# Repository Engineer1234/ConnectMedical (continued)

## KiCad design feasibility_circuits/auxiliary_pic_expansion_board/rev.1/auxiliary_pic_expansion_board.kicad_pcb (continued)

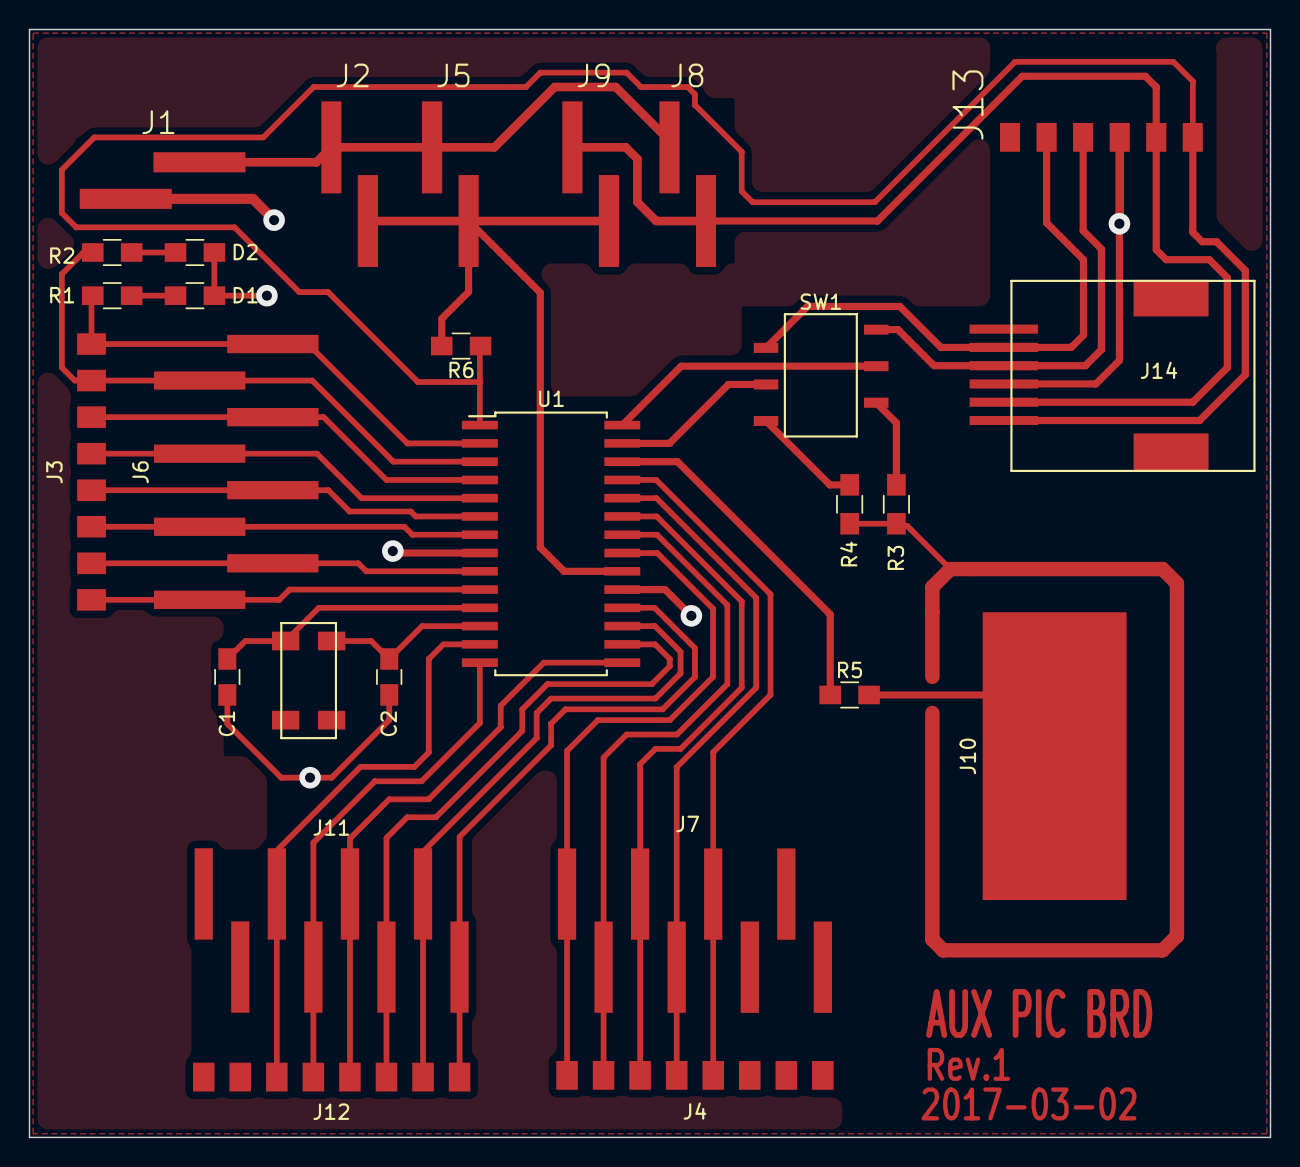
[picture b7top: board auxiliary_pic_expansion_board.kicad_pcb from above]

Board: 2 copper layers, 86.2 x 77.0 mm, 27 parts (0 on the bottom side), 37 nets.

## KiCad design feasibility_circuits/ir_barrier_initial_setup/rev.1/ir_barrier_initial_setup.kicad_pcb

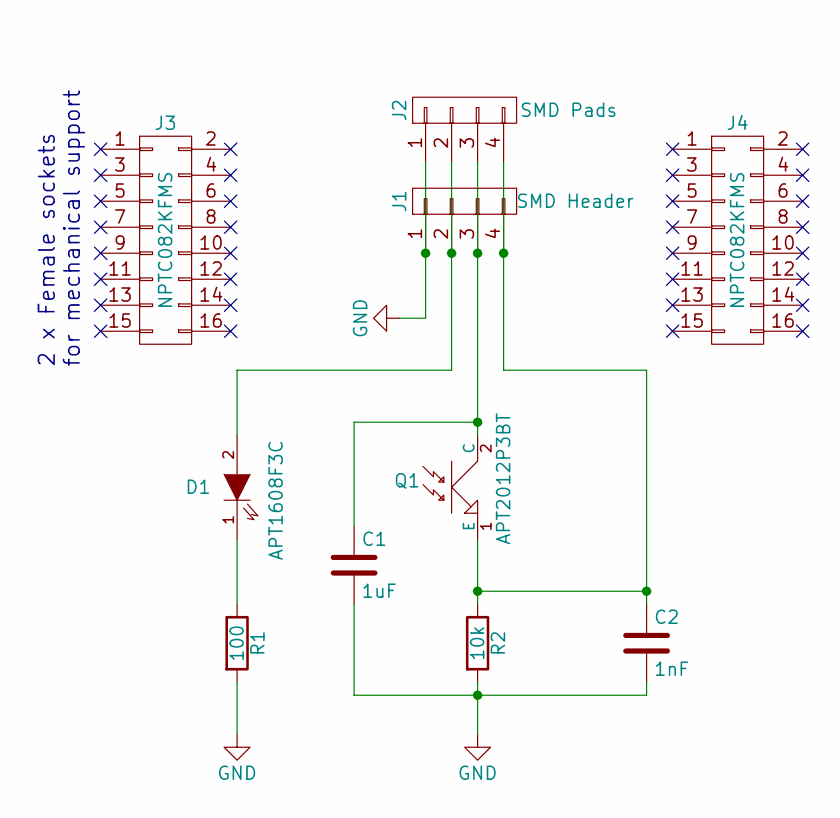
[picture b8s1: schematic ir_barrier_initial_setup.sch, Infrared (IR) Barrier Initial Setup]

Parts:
C1: 1uF; C_0805_HandSoldering
C2: 1nF; C_0805_HandSoldering
D1: APT1608F3C; LED_APT1608F3C
J1: SMD Header; Sullins_SMD_pin_header_1x4_GBC36SABN-M30
J2: SMD Pads; wire_solder_pad_2.54mm_1x4
J3, J4: NPTC082KFMS; Sullins_SMD_2x08_NPTC082KFMS-RC
Q1: APT2012P3BT; Phototransistor_APT2012P3BT
R1: 100; R_0805_HandSoldering
R2: 10k; R_0805_HandSoldering

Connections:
GND: C1.2, C2.2, J1.1, J2.1, R1.2, R2.2
unnamed: C1.1, J1.3, J2.3, Q1.2 (C)
unnamed: C2.1, J1.4, J2.4, Q1.1 (E), R2.1
unnamed: D1.1 (K), R1.1
unnamed: D1.2 (A), J1.2, J2.2

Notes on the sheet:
2 x Female sockets for mechanical support

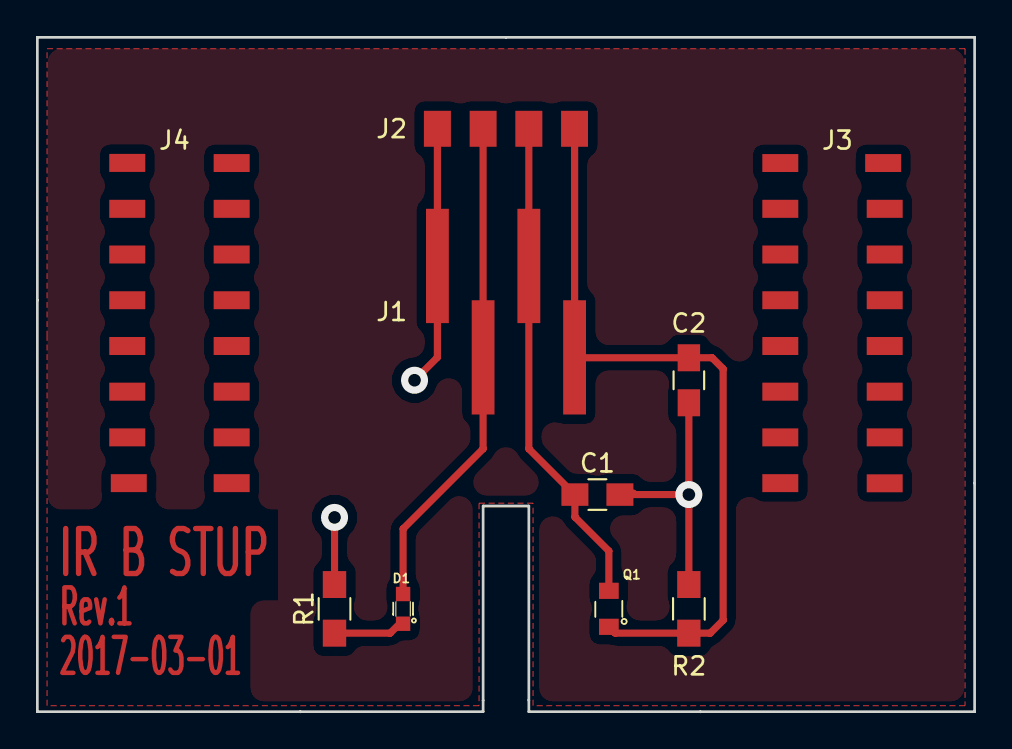
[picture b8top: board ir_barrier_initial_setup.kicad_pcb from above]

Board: 2 copper layers, 52.1 x 37.5 mm, 10 parts (0 on the bottom side), 5 nets.

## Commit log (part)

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2017-02-22 Added schematic for processor board, along with libraries and basic folder structure.
2017-02-22 Addded guard trace for cap-sense pad
2017-02-23 Added prototype board for original IR solution, and imported the Connect Trial footprints in the libraries folder. Also added updated gitignore files for the IR and PIC boards.
2017-02-27 Battery benchmarking
    First commit. Initial infrastructure.
2017-02-28 Battery benchmarking update
    Routed PCB, improvements to structure/naming
2017-02-28 Battery benchmarking update
    PCB ready for review
2017-03-02 Review and organisation
    Review of Auxiliary PIC and IR barrier setup board. Organisation of
    resources.
2017-04-09 2V regulator module
2017-04-18 Four constant current loads module
    Four constant current loads module
2017-04-28 Updated component libraries in battery board to use relative paths
2017-04-28 Finished layout of the TPS61220 regulator board
2017-04-28 Completed initial draft of layout of battery board
2017-04-28 Added holder for Lithium-Ion cell to battery board
2017-04-28 Added files forgotten in last commit.
2017-05-02 Completed schematic for s-1206 LDO prototype board.
2017-05-02 Completed initial draft of layout for S-1206 LDO prototype board
2017-05-03 Added zip files of gerber files sent to Cogra for production for the S-1206 and battery board
2017-05-03 Added gitignore file for feasibility circuits folder
2017-05-03 Removed kicad_pcb-bak files from git version tracking.
2017-05-05 Completed layout of constant current load PCB, the zip file sent for production is also included
2017-05-05 Completed schematic for TPS624731 step-down prototype board
2017-05-05 Created initial project draft for AP3915A 2V regulator prototype board.
2017-05-08 Completed schematic for the AP3915A based 2V regulator prototype board.
2017-05-13 Completed intial draft of TPS627431 2V regulator prototype board
2017-07-26 Created folder Structure. Blank Altium Project. Added Blank Layout File Added Component footprint and symbols. Added Sheet hierarchy with Sheets for: 1.CPU Board 2.Power Management 3.Connectors 4.I/O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
2017-07-26 Test : Updated Block Diagram
2017-07-26 Test commit from Altium
2017-07-26 Test, from Altium
2017-07-27 Create and Update components required on Boost regulator
2017-07-27 - Create extra SCH components for Buck regulator - Update PWR_MGMT Schematics accordingly
2017-07-27 - Create extra SCH components for USB protector and Charger controller - Update PWR_MGMT Schematics accordingly - Todo: Add footprints to PCB library (0402, 0603, etc)
2017-07-27 Altium SVN status Check
2017-07-27 - Update all passive components by adding PCB link ins SCHlib - Update PWR_MGMT with corresponding components
2017-07-27 - Add CPU and connector for OLED on CPU_BRD - Add IR Barrier on IO_BRD - Create components as necesarry and added to SCHLib
2017-07-31 - Add 2.2nF component for Touch sensor in SCHLIB - Add Touch sensor capacitor in CPU_BRD - Label CPU connections in CPU_BRD
2017-07-31 - Create components for battery connector and touch connector - Add Battery connector to PWR_MGMT - Add Touch connector to CPU_BRD
2017-07-31 - Reacommodate Battery connector on CONN - Create (draft) components Programming pads and testing points - Initiate usage of programming pads and testing points in CONN
2017-07-31 (Bug) Correct TP part as No-BOM and update CONN
2017-08-01 Update Touch sensor connector specs using the verified one sent by Oliver Chu
2017-08-02 - Add "DigikeyPartNumber" id in all used components from SCHlib then propagate to project - Create first version of PCB based on the Step file provided (will be updated)
2017-08-03 Update USB connector: Create component and update schematics as well
2017-08-03 - Correct spacing in SCH for IO board - Initialize component PCB placement on EFM1 - Add Cost of components of BOM in new sheet
2017-08-04 - Update component so Digi-Key Part Number use multiples of 1K to buy - Separate component 0603 10uF into 10uF-4V and 10uF-10V - Update Schematics - Update BOM and BOM cost
2017-08-04 - Remove silk layer labels of Cypress Module component - Change layer of all silk layer on PCB Layout
2017-08-08 Add STBC03 component: Li-Ion linear battery charger with LDO and load switches
2017-08-10 - Update PCB with non-hole version in USB section - Finish - Update labels of componenets - Preposition all components to check saturation in the board
2017-08-14 Correct Capacitance in IN and SYS section of Power Management
2017-08-14 Reduce dimensions of 0402 capacitor components so they are IPC High density compliant
2017-08-16 Creation of component for I2C Memory PCA9571GUX & LE2464C: creation of components and usage in Schematics
2017-08-16 Update Testing points and CPU programming points: 1mm pad, 0.6mm via with 0.3mm holes
2017-08-16 Increase current to 89% of Capacity: 34.3mA, by changing ISET resistor to 5.6Kohm
2017-08-16 - Reallocation of components to have a view after the change to I2C components - Update BOM with costs
2017-08-18 - Update PCB board according to latest specifications (2 strips on the side) - Update Light Barrier mechanism: use 0ohm resistors
2017-08-22 - Update circuit for IR barrier - Add testing TRX - Update components - Update position of components on Layout - Update BOM
2017-08-22 - Add R20 to reduce current consumption to MOUNT_SWITCH signal in MCU - Allocate component - Update BOM
2017-08-22 - Keep Buck converter always ON: Connect EN to VIN (Datasheet reference)
2017-08-23 - Apply changes from recommendations on Schematics review: Naming, connections, and specifications of values R1&R2
2017-08-23 - Bug: Use V_BATT on Mount Switch - Create LED components - Create and replace L1 with recommended 10uH
2017-08-24 - Add latest 3D views - Add comments regarding the Mounting Switch
2017-08-24 - Add FET mechanism proposal (parts not finalized)
2017-08-24 cosmetic changes in schematics. Changed Port name for Mounting Switch to Wake_up. Moved USB symbol to Top level. Added RES to Wake up FET Clean up.
2017-08-25 - Update Programming component (5 pins dimensions)
2017-08-25 - Add ESD protection on the switches
2017-08-31 - Correction of description on ESD diode
2017-09-07 Changed File version from “A” to “B” Updated I/O board to remove extra 0 Ohm RES Changed USB connector to USB3155 Added Step files for components
2017-09-07 Adding tag folder
2017-09-07 Changed VDD from 2V to 3V Changed step files and solder mask size on few components
2017-09-07 Added step Files
2017-09-07 Added Note for removed 2V regulator.
2017-09-07 Un-versioned BOM template files Fixing SVN issues
2017-09-13 Project template for EFM1 hybrid board
2017-09-13 Added Test points. Added foot prints for jumpers and GND test points.
2017-09-13 Placed MCU , Modified footprint for LED , need needs to be verified. Added step file for Battery connector.
    //Kartik
2017-09-14 Changed origin to centre of hole Added new component - Touch connector 1003-1009-1-ND placed Fidu placed MCU and Touch conn
2017-09-14 Moved mounting hole and hence the origin too. Added grid lines
2017-09-14 - Add VEMT2003X01 component - Remove STEP from VEMT2003X01, VEMT2000X01, and VSMB2000X01 (still need to find correct reference)
2017-09-14 Buck converter removed from Layout Components made Graphical
2017-09-14 Revision and creation of components: APT1608F3C,APT2012P3BT,TEMD7100X01,VSOP38336,TEMT7100X01,TSOP57256HTT1,VEMT2000X01
2017-09-14 Modified Footprint for BGA , Added via in Pad based on the reference designs from ST modified Footprint for other pars to remove DRC errors
2017-09-15 Updated footprints to remove rule conflicts Updated footprints to remove rule conflicts
2017-09-15 Commit end of the day: IR LED and Switches laid out. 9V regulator.
2017-09-18 Create components: 74AUP1G86FS3-7, Switch toggle, headers 14x2 and 9x2, touch pad and Orange LED
2017-09-18 Update component available provider: headers 14x2
2017-09-19 Swapped the pins on the Batt connector . Finished the layout for Batt charger
2017-09-19 Fixed Missing Step file of enclosure
2017-09-19 Changed Step file for LED.
2017-09-20 Switched wake-up gate voltage from 3V to VCC_VCC. based on Spice simulation Layout
2017-09-20 Values for R & C for Wake up delay set to 82K and 22uF. change in Footprint of the 22uF Cap to 0603
2017-09-20 Layout , Before removing I2C CAPs
2017-09-20 End of day commit
2017-09-21 Added footprint for M24256-DFCS6TP/K 256K memory
2017-09-21 Changed Position of OLED Con. Changed memory.
2017-09-22 Switched SNS_Touch and Ai_LASER_CURRENT pins ( 22 and 14)
2017-09-22 Before swapping LED Pins
2017-09-22 Changed solder mask size on few components due to DRC errors
2017-09-25 Added Draftman files
2017-09-25 Add Step file for VEMT2000, VSMB2000 and VEMT2003X01
2017-09-25 Production files generated. removed Old BOM files.
2017-09-26 Added Testpoint info to Draftman page
2017-09-26 corrected output file name for Assembly Drawings
2017-09-26 Updated PCB based on enclosure Step Files from Even
2017-09-26 latest PCB Rules and DXP Preferences
2017-09-26 re-saved project
2017-09-26 Updated Sch to include extra IR pairs added Jumper headers.
2017-09-26 Update for errors.
2017-09-26 corrected "Unique Identifiers Errors"
2017-09-27 Updated with board shape experiment
2017-09-27 Cosmetic changes to Sch
2017-09-27 Fixed off grid net labels.
2017-09-28 Changed component description for IR LED. Changed from KPT-2012P3BT > APT1608F3C. No changes in layout. Sch, BOM & pick and place files updated as a result.
2017-10-13 changed file name of the BOM
2017-10-18 Latest Files 2017-10-17 15-17-44
2017-10-18 Added Pick Place Output files
2017-10-30 Added Touch PCB Project
2017-11-16 Comin Before edit for Ver 2
2017-11-16 EFM2 baseline commit
2017-11-22 Changes made to SCh : Removed I/O expander Pins from I/O expander moved to Module removed 3 GPIO test points. Swapped pins of USB CON
    Layout changes to reflect the above
2017-11-29 Before change in Shape
2017-11-29 CAM Files created for mighT
2017-12-04 Generated BOM and Pick and place files Made OLED CON a standard BOM item.
2017-12-04 New Gerber Files for MighT
2017-12-04 FP1 Baseline
2017-12-06 Updated description for 10µF ±10% 16V X5R Ceramic Capacitor 0603 it read 16µF before.
2017-12-08 Changes after talk with Mech
2017-12-14 layout near completion , Moved MCU on Even's input
2017-12-19 Test points added for V Batt and 5V PDF's generated Clean up.
2017-12-19 Modified BOM template Gen BOM and Other PDF again. Changed DNP parts to not to appear in BOM
2017-12-20 Generated new Sch Pdf to correct for corrupt file.
2017-12-22 New ver for the touch PCB for FM2
2017-12-22 changed file name to EFP1
2017-12-22 Gerber and Camtastic file
2017-12-22 Gerber and PFD outputs
2017-12-22 Changed CAPs on the 9V bus. moved universal contact upwards. removed the GND universal contact
2017-12-22 Update in Project file
2017-12-25 Clean up commit
2017-12-25 removed Previews
2017-12-25 Updated Pdfs
2018-01-22 Commit before Final design review
2018-01-22 changes asper Review removed CMOD Cap added 0R res to bypass FED for IR LED added 0R res in place of CMOD Cap. Clean up of SCH.
2018-01-22 Cosmetic change step files
2018-01-22 Gerber Output added (Sent to MIGHT for Quote)
2018-01-22 Removing Old Gerber files
2018-01-22 RRemoving Old Gerber files
2018-01-23 Board shaped changed with input from Lance and Ben
2018-01-23 Board clean up and production file generation. removed Solder from DNP components modified Solder mask for some components Generated clean PDFs Assembly drawings cleaned up.
2018-01-26 IR elements moved under Light guide. Board shape changed slightly to accommodate IR receiver on the edge of the board. changed footprint of IR receiver. touch PCB to be changed to FPC; Universal conn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
2018-02-09 Board updated to Flex Touch Ver 3
2018-02-22 pick n place files updated
2018-02-22 project file updated.
2018-03-06 SCH Cleanup Project files .
2018-03-06 Proj cleanup.
